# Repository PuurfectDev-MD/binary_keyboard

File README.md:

# Binary Keyboard

This is wacky, silly project where you can type your keyboard inputs in binary and send it to a connected device. You can enter the byte values (8 switches represent 8 bits in a byte) which represents a character. Then you confirm your input with the enter switch to covert that binary byte to a character to send to your device (wired or wireless!). Basically a keyboard but you type in binary because why not! It uses the SuperMini nRF52840 mcu ( a nice!nano clone) which supports bluetooth connectivity for you to send your inputs wirelessly.

## Motivation
I build the binary keyboard just for the sake of learning. No other motives. Its just a very stupid and fun idea which struck me and there I went building :)

## PCB

## 3D case

##  Project Structure

```text
├── 📁 3d_models
│   ├── 📁 Fusion 360     # Contains the .f3d files and STEP files
│   └── 📁 PCB export     # The 3d file exported from KiCad
├── 📁 KiCad              # Contains the KiCad schematics and PCB files 
├── 📁 Firmware
│   ├── 📁 Circuit Python # Contains the uf2 file that is to be flashed to the supermini
│   ├── 📁 lib            # Contains a zip file for the circuitpython firmware
│   └── 📄 code.py        # Contains the main code
└── 📁 BOM
    ├── 📄 kicad.csv      # KiCad generated CSV (no price present)
    └── 📄 BOM.cBOM mnaully created with price and total estimation
```

## How it works 
There are an array of 8 switches that are connected to the GPA0 to GPA7 of the MCP23017 gpio expander. The GPB0 has three connections - (SPACE, BACKSPACE and ENTER). There are intrerrupts for both of them which are conencted to gpios of the mcu. Whenever a user presses a button (any of the 8 buttons that repsresnt 1 bit of a byte for a single char) the state is changed for that bit's value. So if it was a 0 it changes to 1. Like that we can toggle each of the bits state and at the end press the enter button to confirm the data input. Then the python script (code.py) converted the byte to a char by mapping it to a character and returns it to the USB_HID device for it to be printed on your screen.

## How to make it work for you
First print the PCB. Print the 3d case. Then solder the parts in place. For the firmware- flash the uf2 file in the supermini. Then install the firmware into the mcy by unzippping the file inside /Firmware/lib. And upload the code.py file to begin testing and using the device.    

## AI USE
For firmware guidance and the code.py file code. Teensy help on fusion on selecting screw and other minor stuff. And small help for debugging kicad schematic and suggestions for improvements.

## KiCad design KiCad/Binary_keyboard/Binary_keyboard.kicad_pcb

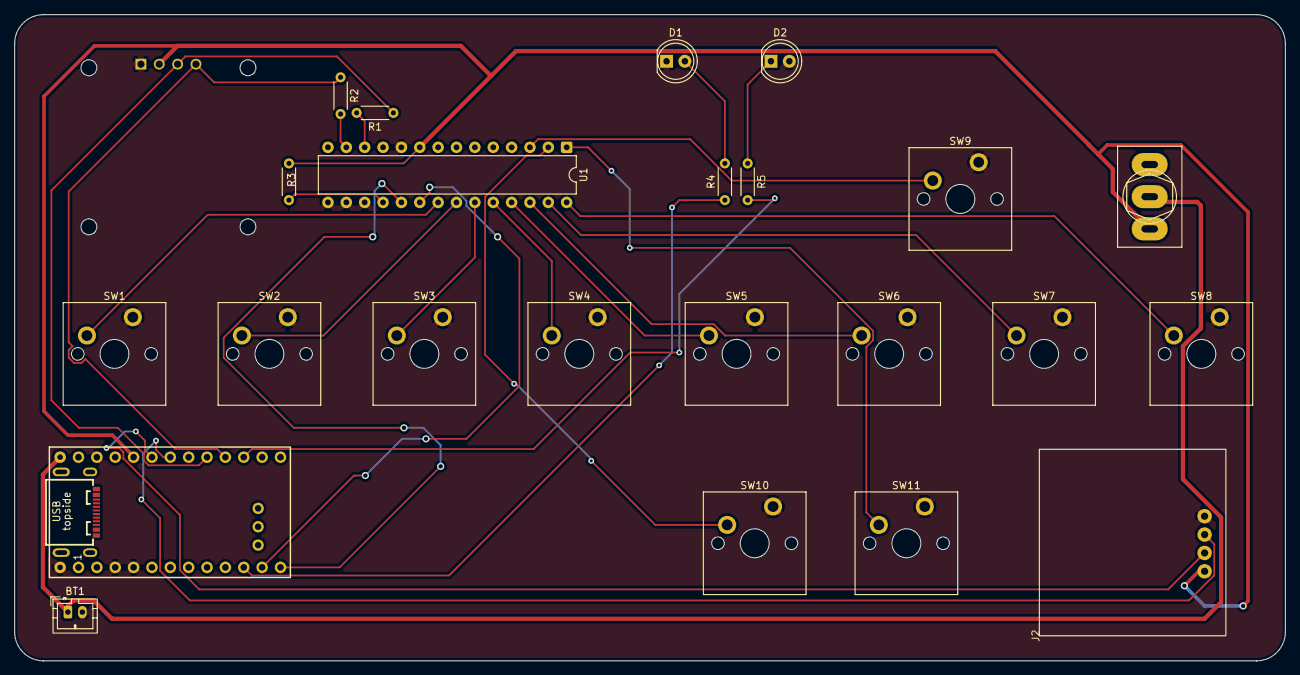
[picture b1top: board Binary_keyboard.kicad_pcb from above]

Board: 2 copper layers, 175.8 x 89.4 mm, 24 parts (0 on the bottom side), 27 nets.

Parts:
BT1: Battery_Cell; JST_PH_B2B-PH-K_1x02_P2.00mm_Vertical
D1, D2: LED; LED_D5.0mm
J1: OLED_128x64
J2: Conn_01x04_Pin; footprint25.8 * 25.8
R1, R2: 4.7k; R_Axial_DIN0204_L3.6mm_D1.6mm_P5.08mm_Horizontal
R3: 10k; R_Axial_DIN0204_L3.6mm_D1.6mm_P5.08mm_Horizontal
R4, R5: 300; R_Axial_DIN0204_L3.6mm_D1.6mm_P5.08mm_Horizontal
SW1, SW2, SW3, SW4, SW5, SW6, SW7, SW8, SW9, SW10, SW11: Switch; MX_PCB_1.00u
SW12: SW_Nidec_CAS-120A1; SW_Toggle_Blue_wSlots
U1: MCP23017x-x-SP; DIP-28_W7.62mm
U2: SuperMini nRF52840; SuperMini NRF52840

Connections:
+3V3: J1.2 (VCC), J2.1, R3.1, SW12.3 (A), U1.9 (V_{DD}), U2.16 (3V3)
BAT+: BT1.1 (+), SW12.2 (B), U2.29 (BAT+)
BCKSPC: SW9.1, U1.3 (GPB2)
BIT_1: SW1.1, U1.21 (GPA0)
BIT_2: SW2.1, U1.22 (GPA1)
BIT_3: SW3.1, U1.23 (GPA2)
BIT_4: SW4.1, U1.24 (GPA3)
BIT_5: SW5.1, U1.25 (GPA4)
BIT_6: SW6.1, U1.26 (GPA5)
BIT_7: SW7.1, U1.27 (GPA6)
BIT_8: SW8.1, U1.28 (GPA7)
ENTER: SW10.1, U1.2 (GPB1)
GND: BT1.2 (-), D1.1 (K), D2.2 (A), J1.1 (GND), J2.4, SW1.2, SW2.2, SW3.2, SW4.2, SW5.2, SW6.2, SW7.2, SW8.2, SW9.2, SW10.2, SW11.2, U1.10 (V_{SS}), U1.15 (A0), U1.16 (A1), U1.17 (A2), U2.3 (GND), U2.4 (GND), U2.14 (GND), U2.28 (GND)
INT_A: U1.20 (INTA), U2.11 (P1.04-LF)
INT_B: U1.19 (INTB), U2.12 (P1.06-LF)
LED1: R5.2, U2.22 (P1.11-LF)
LED2: R4.1, U2.10 (P0.11)
unnamed: D1.2 (A), R4.2
unnamed: D2.1 (K), R5.1
unnamed: R1.2, U1.12 (SCK)
unnamed: R2.2, U1.13 (SDA)
unnamed: R3.2, U1.18 (~RESET)
SCK: J1.3 (SCL), R1.1, U2.20 (P1.15-LF)
SDA: J1.4 (SDA), R2.1, U2.21 (P1.13-LF)
SPACE: SW11.1, U1.1 (GPB0)
X: J2.2, U2.17 (P0.31-LF)
Y: J2.3, U2.18 (P0.29-LF)

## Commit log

2026-05-12 First commit - schematic setup
2026-05-14 Case and zine
2026-05-15 Zine update
2026-05-19 Added firmware, BOM and README.md update
2026-06-07 Added assembly file and removed backup files
2026-06-07 STL files
